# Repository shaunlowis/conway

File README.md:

# conway
Using my own implementation of Conway's game of life to learn more about embedded software.

# Notes to the weary traveler
- If you want to repeat this project, first order your cherry MX keys, then check the PCB layout.
  For me, the connector pins were on different locations than the schematic file I got. Update this afterwards.
- It is extremely unlikely that your LCD will have the same pinouts as mine, double check this part.
- My LCD's pins aren't in the middle of the PCB (Check the final image), if you care about this, you might want
  to adjust the location of the pins so the buttons are neatly aligned under the screen.

## Goal/Overview

- The PCB itself is supposed to just be a nice bit of desk decoration. It can all be powered
from a USB cable, connected to the STM. 
- Started out with a basic design to perpetually render Conway's game of life on an LCD
screen. Naturally scope creep ensued:
    - Made a custom PCB for mounting the screen and connecting to it.
    - Added buttons and LEDs for different rules to use.
    - Figured keyboard keys would work quite well for this. Updated PCB accordingly
- Wound up with a relatively useful shield that can be repurposed for future projects.

First version:
<details>
<summary> Initial breadboard layout</summary>

</details>

### Arduino support
The standard Arduino Uno does not have enough on-board memory to support a 128x64 pixel display.
In my case, pictured above, I wanted to release a version of this code that works easily for the average user.
Hence reducing the screen size to 64x36 is the largest section that we can run with a simple approach to Conway's game of life.

### Python demo
The software for Conway's game of life, for a basic python version and Arduino can be found in `/software`.

### LCD Screen config
The U8G2 Arduino library has a large amount of support for LCD screens, available [here](https://github.com/olikraus/u8g2/wiki/u8g2setupcpp). I used the `ST7920_128X64` module.

Refer to the LCD datasheet in `/circuitry` for wiring.

### STM Nucleo
On an STM32 NULCEO-F411RE, with more memory, the full 128x64 LCD screen is easily rendered.
I have made a shield that the screen can connect to directly using kicad 7. 
These files can be found under `/circuitry/kicad`. 

Install the Arduino library, then STM Core library from [here](https://github.com/stm32duino/Arduino_Core_STM32).

Great documentation on installing STM support [here](https://github.com/stm32duino/Arduino_Core_STM32/wiki/Getting-Started).

Summary of above STM install:

Install the STM Cube programmer software (required), from [here](https://www.st.com/en/development-tools/stm32cubeprog.html#get-software).
You will need to check your email for the download link to the above.

You can go to File -> Preferences -> Additional boards manager URLs, paste the link in the above documentation here.

Then click the Boards Manager icon, type "STM", then install "STM32 MCU based boards".

We can now go to "Select Board" --> Easiest to connect the STM to your PC and check its name. For me, I selected Nucleo-64.

Make sure you additionally select the correct board part number! This caught me out initially. This is in the "Tools" drop-down menu.
You can plug in your STM to your PC and open the `MBED` file, which opens a webpage with details on the model number and so-on.
If you don't have network access, your board should show up with the part number as its name as a drive in your PC.

Finally, the code uses the U8g2lib, which can be installed with: Library Manager --> search "U8g2", install first result.

<details>
<summary> First, basic layout</summary>

Example wiring.
Barebones only display updating is in `conway_stm64.ino` for full display and a counter of generations.

</details>

#### Adding buttons

Additionally, buttons and LEDs were added so the user can choose different rulesets to use
for Conway's game of life. Pictured below is the "white" LED shining from selecting the
Morley's miracle rules, by clicking the white button.

We now also have a more elegant PCB with support for Cherry MX keys:
I found [these](https://www.digikey.co.nz/en/products/detail/cherry-americas-llc/MX1A-E1NW/20180) 
on Digikey that had nice 3D files. This yielded the screenshot in the Overview section.

## Final PCB with screen:

### TODO:
Hardware:
- Make a 3D-printed case for this, done on onshape, the .stl will be added in `/enclosure`.
- Keycaps are stupdidly expensive on Digikey, at $9 each. I should 3D print some, will also add to above folder.

Software:
- Add support for the cherry keys as they don't have resistors. See [here](https://docs.arduino.cc/tutorials/generic/digital-input-pullup/).
- Add in a button press combination to restart the simulation.
- Weird bug where pulling the power on the card fills the screen with chinese characters? Doing a reset loads graphics properly.
      - Honestly this is pretty funny so might not try to diagnose.

Reference file structure:
```
.
├── circuitry
├── enclosure
├── img
└── software
```

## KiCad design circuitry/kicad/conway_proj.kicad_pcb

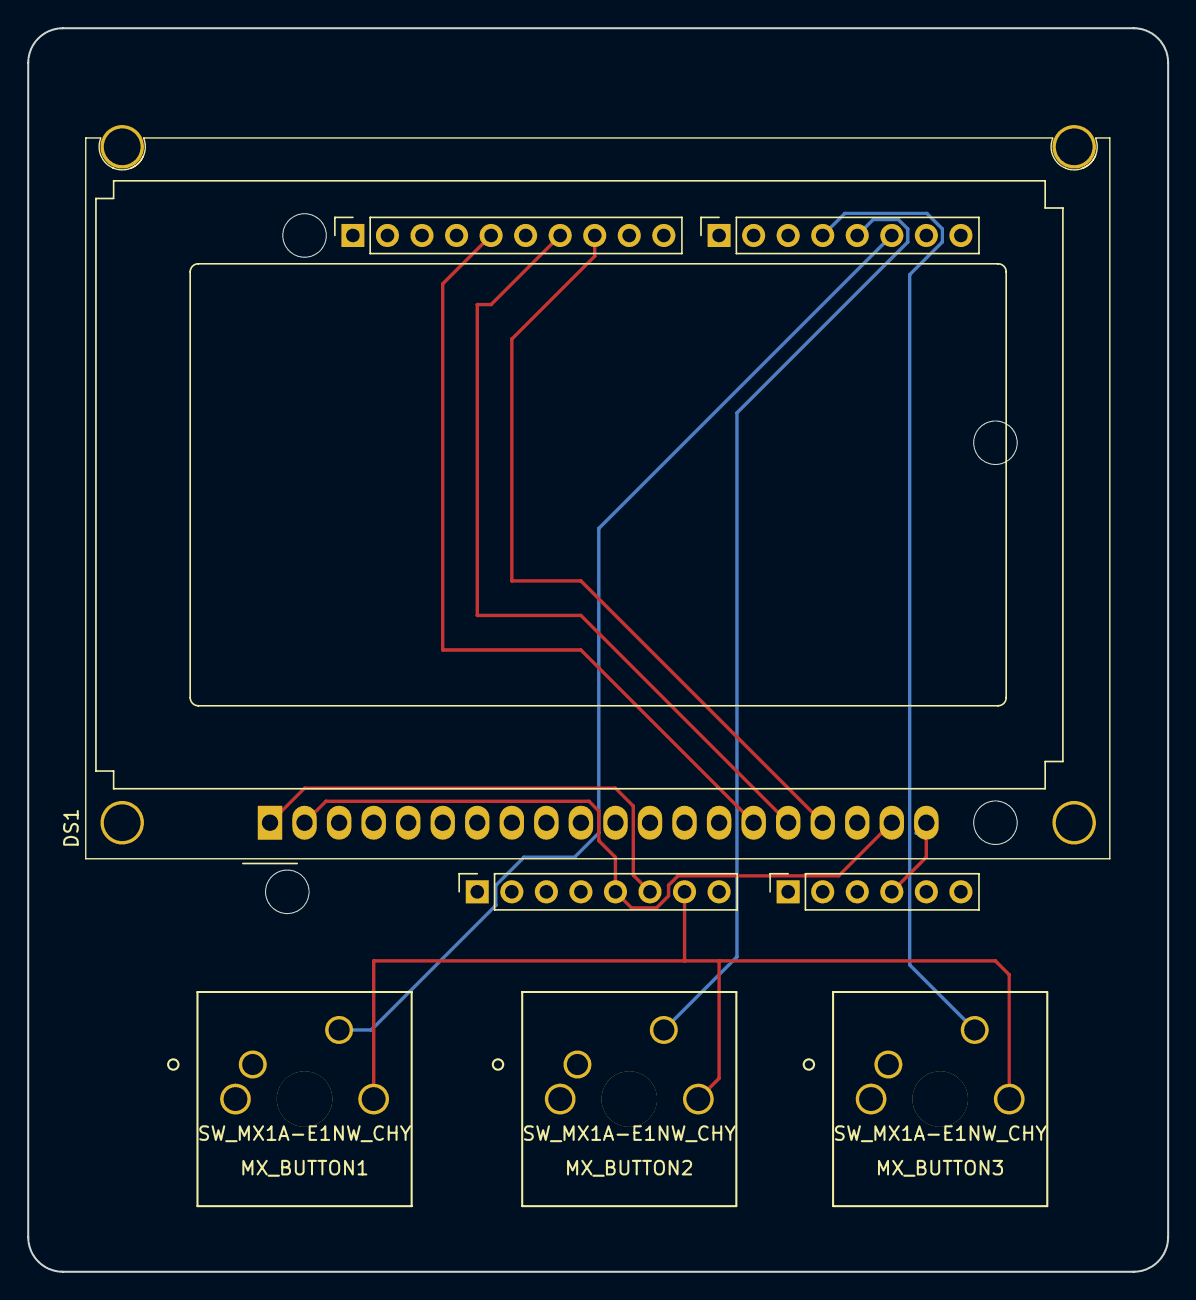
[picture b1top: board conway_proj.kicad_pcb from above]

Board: 2 copper layers, 83.8 x 91.4 mm, 12 parts (0 on the bottom side), 11 nets.

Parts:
DS1: ST7920; AG12864E
J1: Power; PinSocket_1x08_P2.54mm_Vertical
J2: Digital/PWM; PinSocket_1x10_P2.54mm_Vertical
J3: Analog; PinSocket_1x06_P2.54mm_Vertical
J4: Digital/PWM; PinSocket_1x08_P2.54mm_Vertical
MH1, MH2, MH3, MH4: MountingHole_3.2mm
MX_BUTTON1, MX_BUTTON2, MX_BUTTON3: SW_MX1A-E1NW_CHY; MX1A-E1NW

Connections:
+5V: DS1.2 (GND), DS1.19 (LEDA/EL), J1.5
/2: J4.6, MX_BUTTON1.2
/4: J4.4, MX_BUTTON3.2
/13: DS1.15 (R/~W), J2.5
/*3: J4.5, MX_BUTTON2.2
/*10: DS1.17 (E), J2.8
/*11: DS1.16 (D/~I), J2.7
/SCL/A5: J2.1, J3.6
/SDA/A4: J2.2, J3.5
/passive: DS1.3 (VO), DS1.4 (DB0), DS1.5 (DB1), DS1.7 (DB3), DS1.8 (DB4), DS1.9 (DB5), DS1.10 (DB6), DS1.11 (DB7), DS1.12 (~CS1), DS1.13 (~CS2), DS1.14 (~RST), DS1.18 (VEE)
GND: DS1.1 (VCC), DS1.6 (DB2), DS1.20 (LEDK/EL), J1.6, J1.7, J2.4, J3.4, MX_BUTTON1.5, MX_BUTTON2.5, MX_BUTTON3.5

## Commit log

2023-10-07 updated file structure
2023-10-18 hopefully finished circuitry
2023-10-18 Generated step file for making enclosure.
2023-10-20 added some comments, plotting fix.
2023-10-29 Tidying up images.
2023-11-05 Create conway_stm64_buttons_leds.ino
    This version adds support for buttons, LEDs and different rulesets.
2023-11-05 Create debug_buttons_leds.ino
    This was useful to see if the wiring and so on of my breadboard was correct.
2024-02-10 New KiCad version and README updates
2024-02-10 Included new gerber files and updated layout
2024-03-19 Updated PCB layout, fixed 5V and ground to LCD connections.

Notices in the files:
parts and their libraries:
Copyright 2016 Accelerated Designs. All rights reserved.
